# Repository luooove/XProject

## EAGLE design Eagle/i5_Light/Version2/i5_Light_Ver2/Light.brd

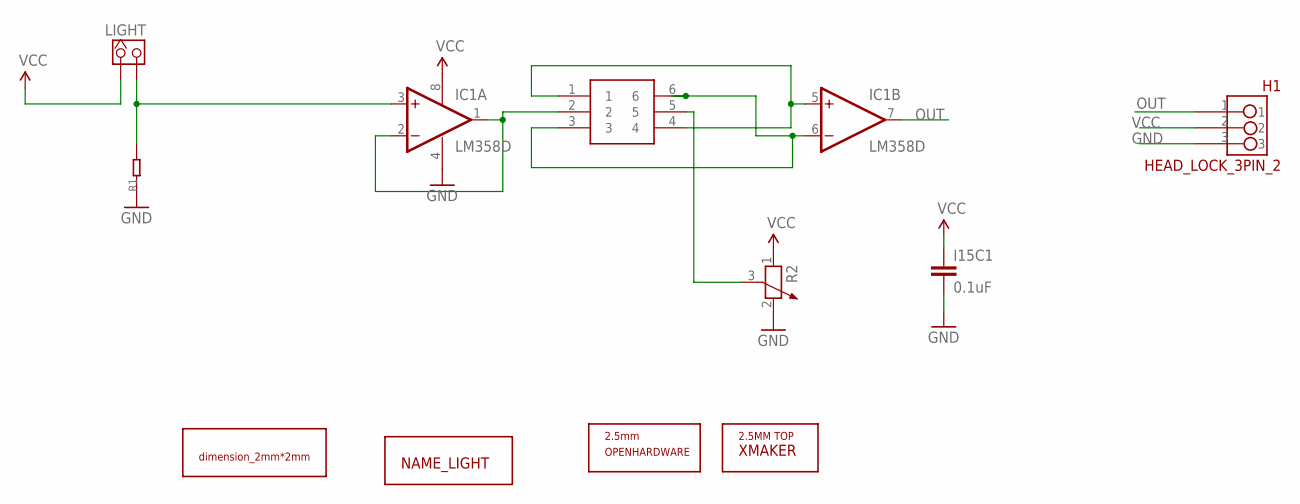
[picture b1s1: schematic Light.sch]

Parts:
H1: HEAD_LOCK_3PIN_2
I15C1: 0.1uF; 0603-CAP
IC1: LM358D; SO08
LIGHT: HEADER_1X2_2.54; CK_1*2
R1: R0603; 0603
R2: R-POTENTIOMETER3362; 3P-SQUA-7X6.8
U$1: DIMENSION_2MM2MM; DIMENSION_2MM*2MM
U$2: NAME_LIGHT
U$3: OPENHARDWARE_2.5MM_TOP; OPENSOURCELOGO_2.5MM
U$4: XMAKERLOGO_2.5MM_TOP
U$5: MSS-22C02

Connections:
GND: H1.3, I15C1.2, IC1.4 (V-), R1.1, R2.2
unnamed: IC1.1 (OUT), IC1.2 (-IN), U$5.2
unnamed: IC1.3 (+IN), LIGHT.2, R1.2
unnamed: IC1.5 (+IN), U$5.1, U$5.4
unnamed: R2.3, U$5.5
unnamed: IC1.6 (-IN), U$5.3, U$5.6
OUT: H1.1, IC1.7 (OUT)
VCC: H1.2, I15C1.1, IC1.8 (V+), LIGHT.1, R2.1

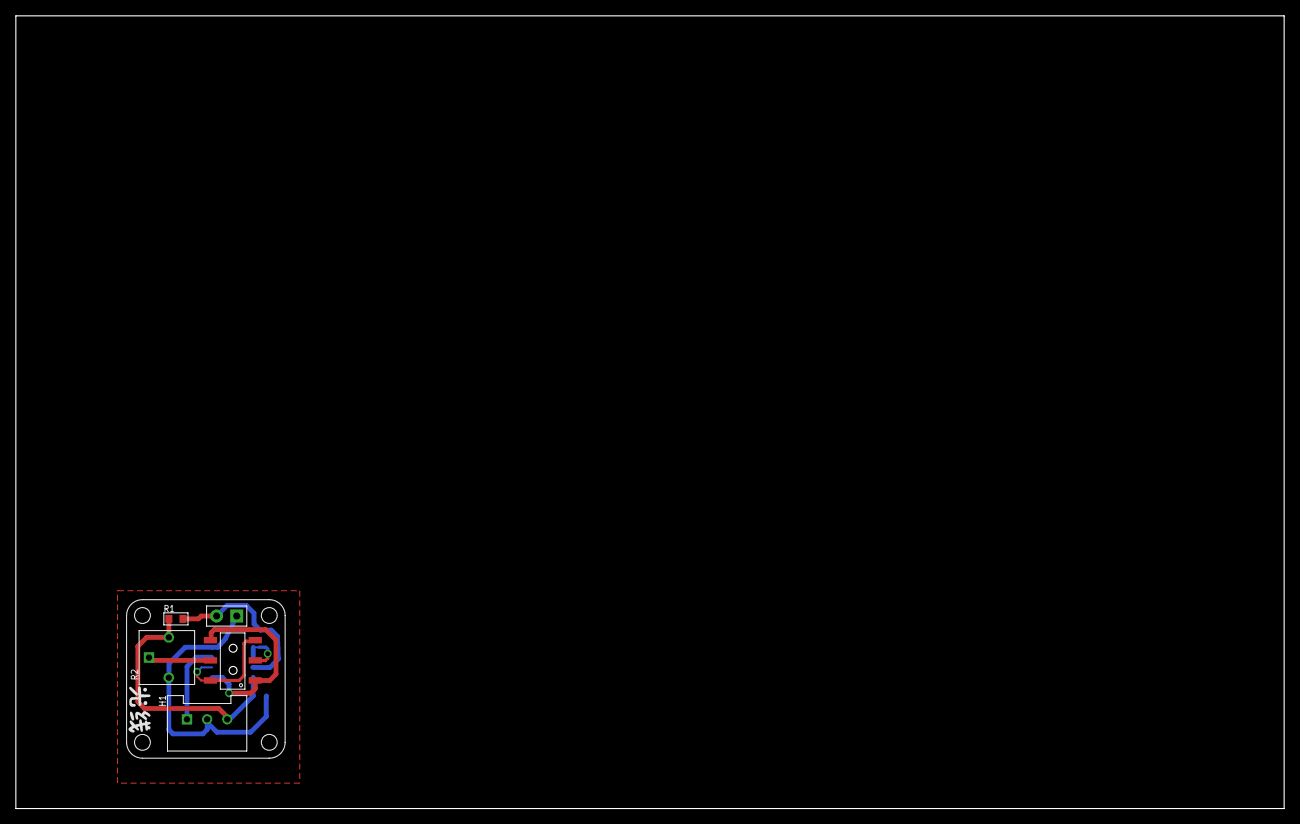
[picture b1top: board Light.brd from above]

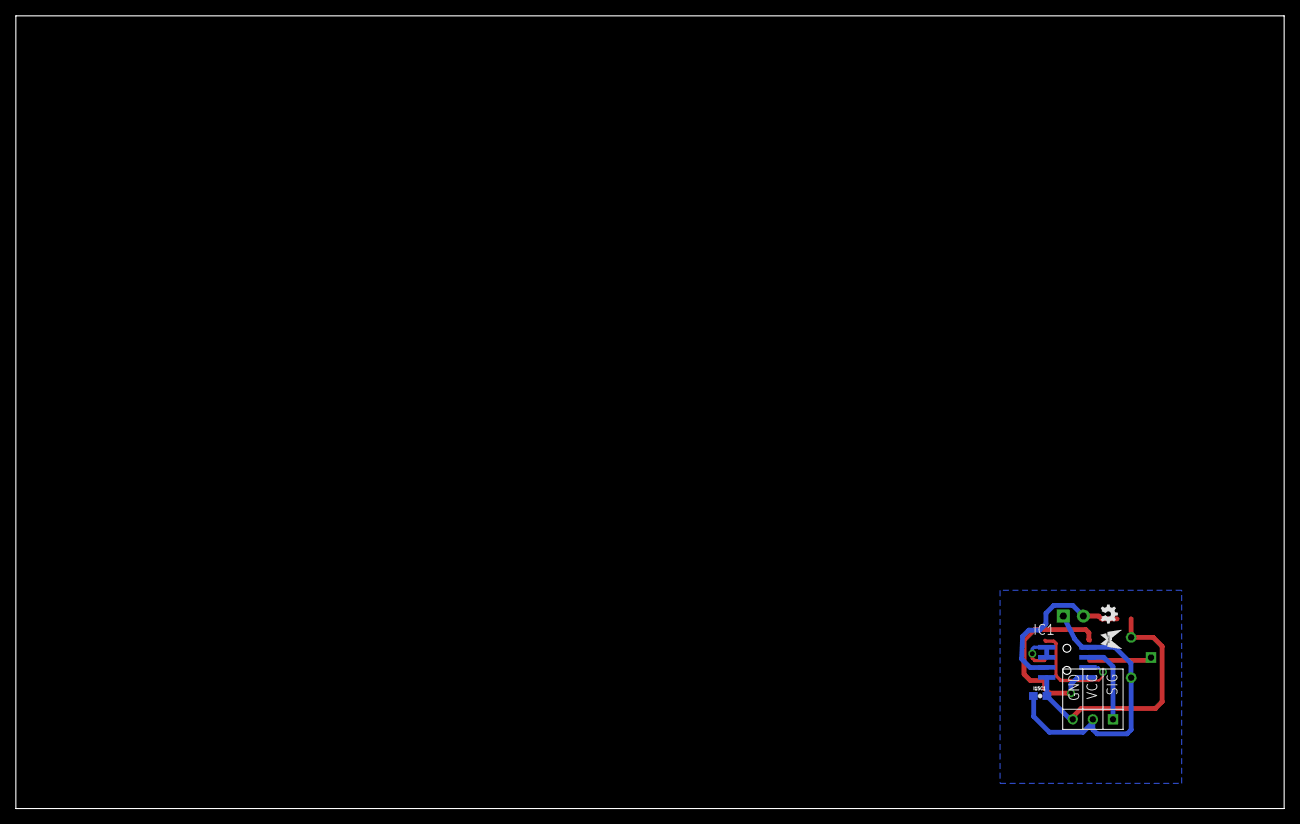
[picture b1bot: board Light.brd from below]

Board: 2 copper layers, 160.0 x 100.0 mm, 11 parts (4 on the bottom side), 8 nets.

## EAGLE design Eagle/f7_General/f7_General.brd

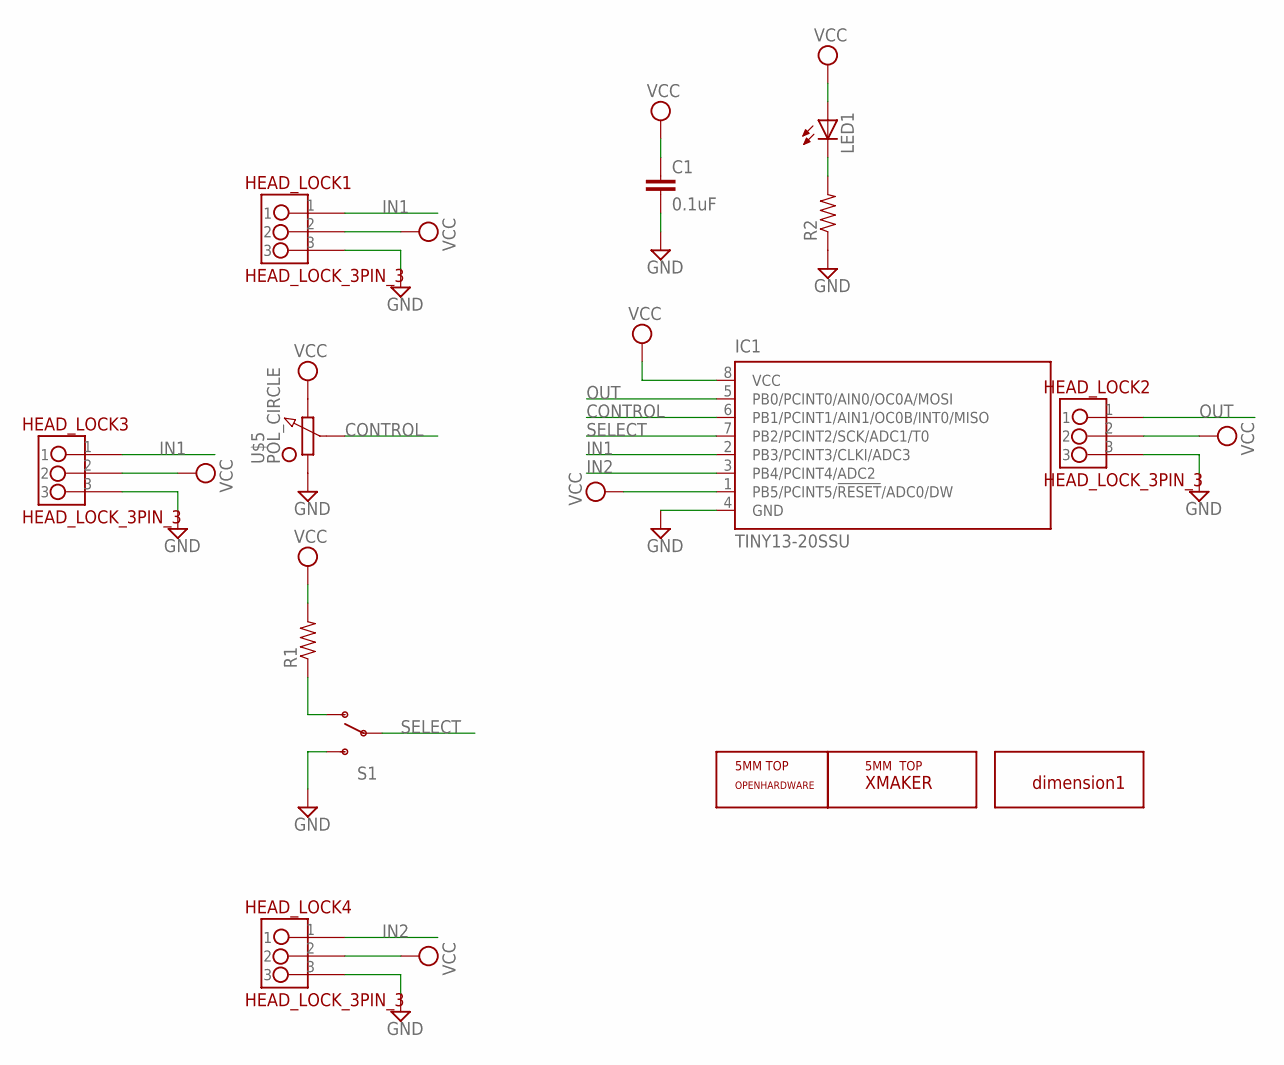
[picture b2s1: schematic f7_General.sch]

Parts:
C1: 0.1uF; 0603-CAP
HEAD_LOCK1, HEAD_LOCK2, HEAD_LOCK3, HEAD_LOCK4: HEAD_LOCK_3PIN_3
IC1: TINY13-20SSU; 8S1
LED1: LED_ESML0603; LED_SML0603
R1: RESISTOR0603-RES; 0603-RES
R2: 0.27OHM-1/10W-1%(0603); 0603-RES
S1: SWITCH-SPDTKIT; SWITCH-SPDT_KIT
U$2: XMAKERLOGO_5MM_TOP
U$3: DIMENSION1
U$4: OPENHARDWARE_5MM_TOP; OPENSOURCE_5MM_TOP
U$5: POL_CIRCLE; POT_CIRCLE

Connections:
CONTROL: IC1.6 (PB1/PCINT1/AIN1/OC0B/INT0/MISO), U$5.P$2 (2)
GND: C1.2, HEAD_LOCK1.3, HEAD_LOCK2.3, HEAD_LOCK3.3, HEAD_LOCK4.3, IC1.4 (GND), R2.1, S1.3 (S), U$5.P$3 (3)
IN1: HEAD_LOCK1.1, HEAD_LOCK3.1, IC1.2 (PB3/PCINT3/CLKI/ADC3)
IN2: HEAD_LOCK4.1, IC1.3 (PB4/PCINT4/ADC2)
unnamed: LED1.C, R2.2
unnamed: R1.1, S1.1 (O)
OUT: HEAD_LOCK2.1, IC1.5 (PB0/PCINT0/AIN0/OC0A/MOSI)
SELECT: IC1.7 (PB2/PCINT2/SCK/ADC1/T0), S1.2
VCC: C1.1, HEAD_LOCK1.2, HEAD_LOCK2.2, HEAD_LOCK3.2, HEAD_LOCK4.2, IC1.1 (PB5/PCINT5/!RESET!/ADC0/DW), IC1.8 (VCC), LED1.A, R1.2, U$5.P$1 (1)

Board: 2 copper layers, 14 parts (0 on the bottom side), 9 nets, no tracks yet.

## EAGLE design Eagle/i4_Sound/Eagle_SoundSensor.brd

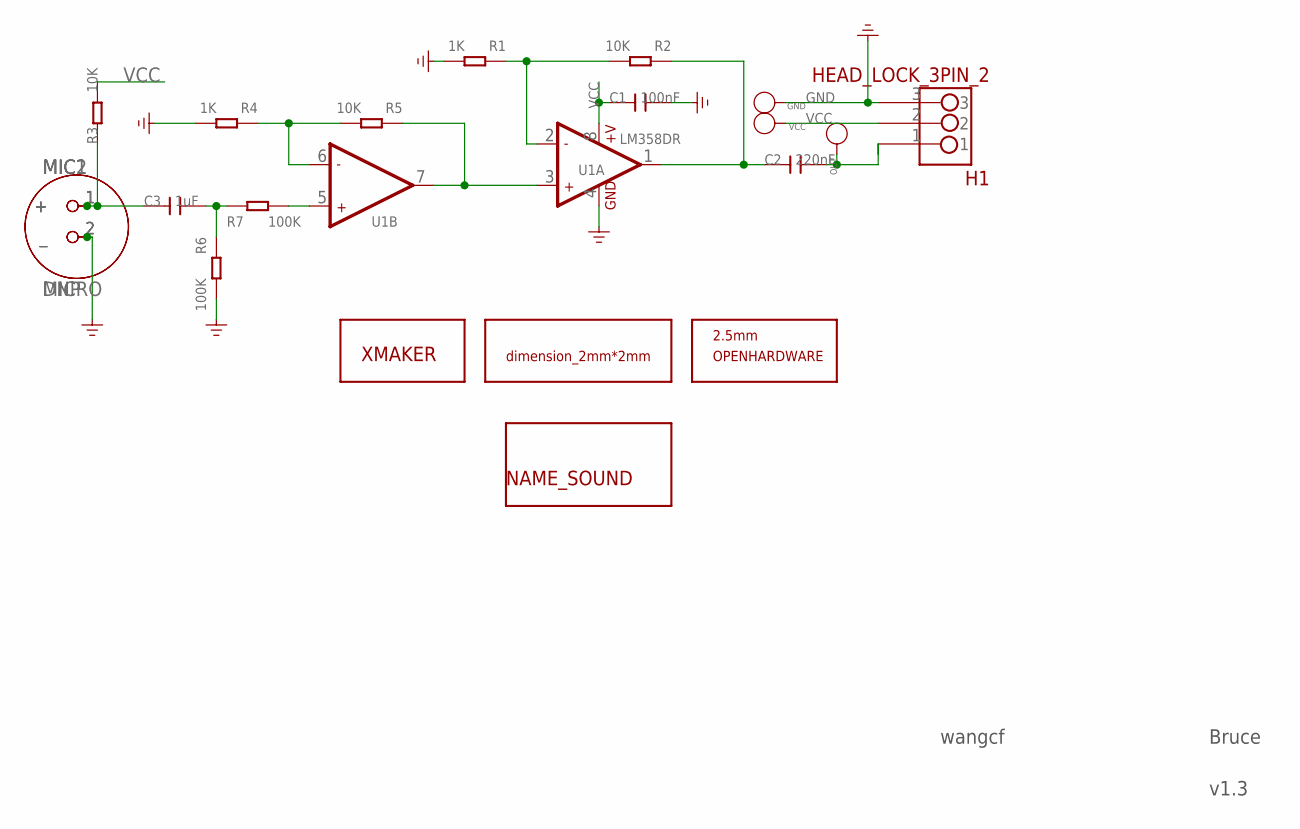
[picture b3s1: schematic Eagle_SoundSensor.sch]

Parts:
C1: 100nF; C0603
C2: 220nF; C0603
C3: 1uF; C0603
GND: PAD-TEST-POINT'4545'; TP_4545
H1: HEAD_LOCK_3PIN_2
MIC1: MICRO
MIC2: DNP; MICRO
OUT: PAD-TEST-POINT'4545'; TP_4545
R1, R4: 1K; R0603
R2, R3, R5: 10K; R0603
R6, R7: 100K; R0603
U1: LM358DR; SO08
U$7: XMAKERLOGO
U$11: DIMENSION_2MM2MM; DIMENSION_2MM*2MM
U$12: OPENHARDWARE_2.5MM_TOP; OPENSOURCELOGO_2.5MM
U$13: NAME_SOUND
VCC: PAD-TEST-POINT'4545'; TP_4545

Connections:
GND: C1.2, GND.T, H1.3, MIC1.2 (_), MIC2.2 (_), R1.2, R4.2, R6.2, U1.4 (GND)
unnamed: R7.2, U1.5 (+IN2)
unnamed: R4.1, R5.2, U1.6 (-IN2)
unnamed: C3.2, R6.1, R7.1
unnamed: C3.1, MIC1.1 (+), MIC2.1 (+), R3.1
unnamed: R5.1, U1.3 (+IN1), U1.7 (OUT2)
unnamed: R1.1, R2.2, U1.2 (-IN1)
OUT: C2.2, H1.1, OUT.T
OUT1: C2.1, R2.1, U1.1 (OUT1)
VCC: C1.1, H1.2, R3.2, U1.8 (+V), VCC.T

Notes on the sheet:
wangcf
Bruce
v1.3

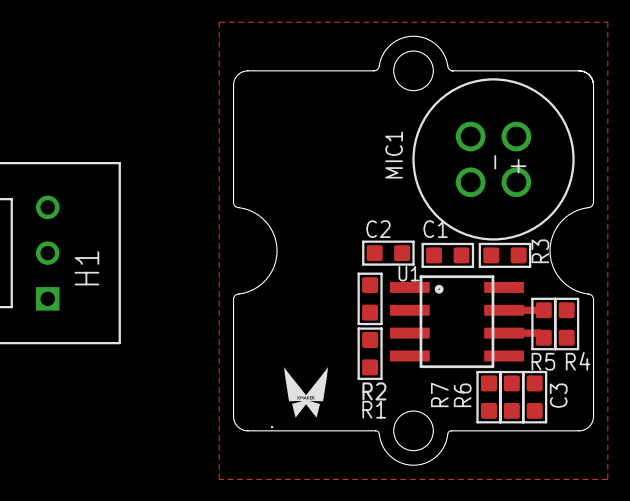
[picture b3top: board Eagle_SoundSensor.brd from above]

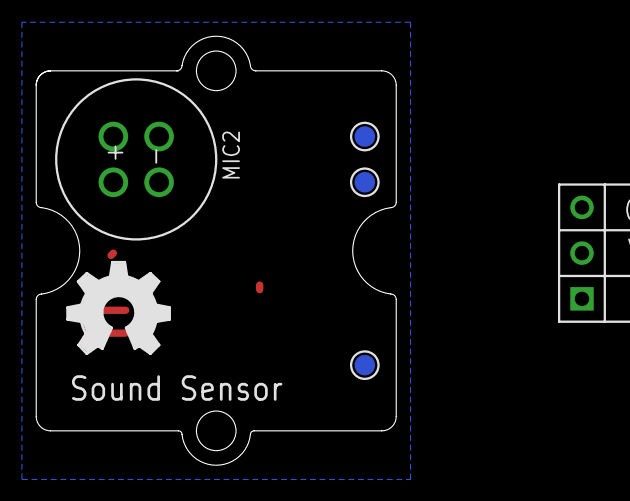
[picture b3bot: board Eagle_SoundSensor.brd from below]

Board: 2 copper layers, 20.0 x 23.8 mm, 23 parts (5 on the bottom side), 10 nets.

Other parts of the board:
U$1: OSHW_FILLX200_NOTEXT
U$4: 1U-DIM-W/-DRILL

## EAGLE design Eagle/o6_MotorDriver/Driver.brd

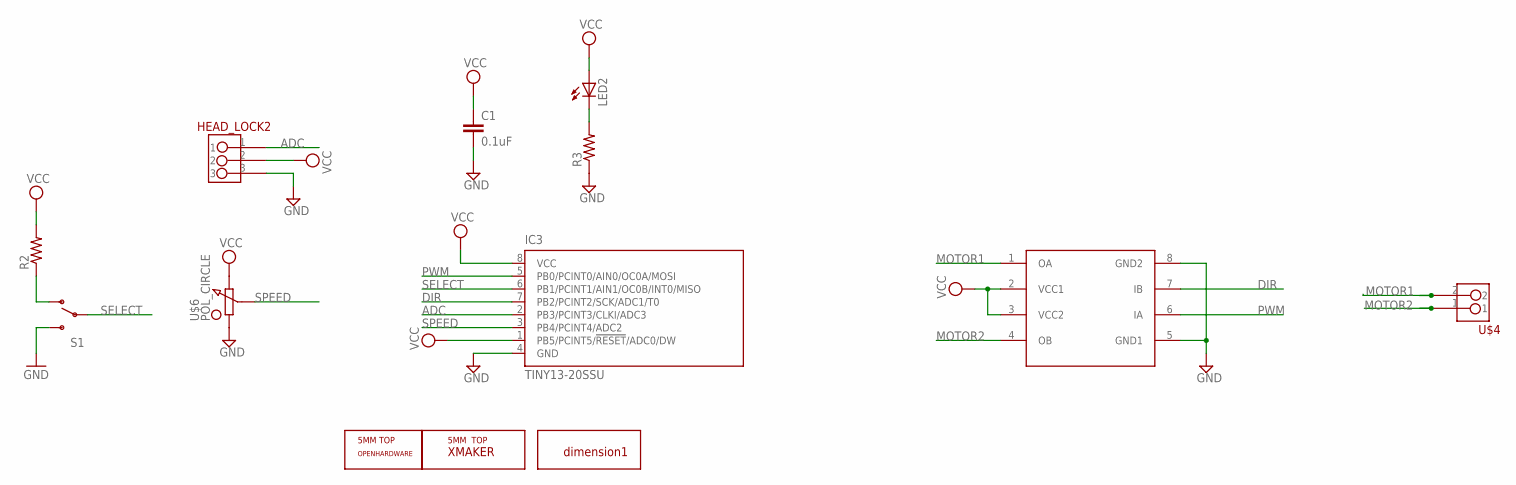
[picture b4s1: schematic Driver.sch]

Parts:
C1: 0.1uF; 0603-CAP
HEAD_LOCK2: HEAD_LOCK
IC3: TINY13-20SSU; 8S1
LED2: LED_ESML0603; LED_SML0603
R2: RESISTOR0603-RES; 0603-RES
R3: 0.27OHM-1/10W-1%(0603); 0603-RES
S1: SWITCH-SPDTKIT; SWITCH-SPDT_KIT
U$1: DIMENSION1
U$2: L9110; SOP8
U$4: HEAD_LOCK2
U$6: POL_CIRCLE; POT_CIRCLE
U$7: XMAKERLOGO_5MM_TOP
U$8: OPENHARDWARE_5MM_TOP; OPENSOURCE_5MM_TOP

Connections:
ADC: HEAD_LOCK2.1, IC3.2 (PB3/PCINT3/CLKI/ADC3)
DIR: IC3.7 (PB2/PCINT2/SCK/ADC1/T0), U$2.7 (IB)
GND: C1.2, HEAD_LOCK2.3, IC3.4 (GND), R3.1, S1.3 (S), U$2.5 (GND1), U$2.8 (GND2), U$6.P$3 (3)
MOTOR1: U$2.1 (OA), U$4.2
MOTOR2: U$2.4 (OB), U$4.1
unnamed: R2.1, S1.1 (O)
unnamed: LED2.C, R3.2
PWM: IC3.5 (PB0/PCINT0/AIN0/OC0A/MOSI), U$2.6 (IA)
SELECT: IC3.6 (PB1/PCINT1/AIN1/OC0B/INT0/MISO), S1.2
SPEED: IC3.3 (PB4/PCINT4/ADC2), U$6.P$2 (2)
VCC: C1.1, HEAD_LOCK2.2, IC3.1 (PB5/PCINT5/!RESET!/ADC0/DW), IC3.8 (VCC), LED2.A, R2.2, U$2.2 (VCC1), U$2.3 (VCC2), U$6.P$1 (1)

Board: 2 copper layers, 13 parts (0 on the bottom side), 11 nets, no tracks yet.

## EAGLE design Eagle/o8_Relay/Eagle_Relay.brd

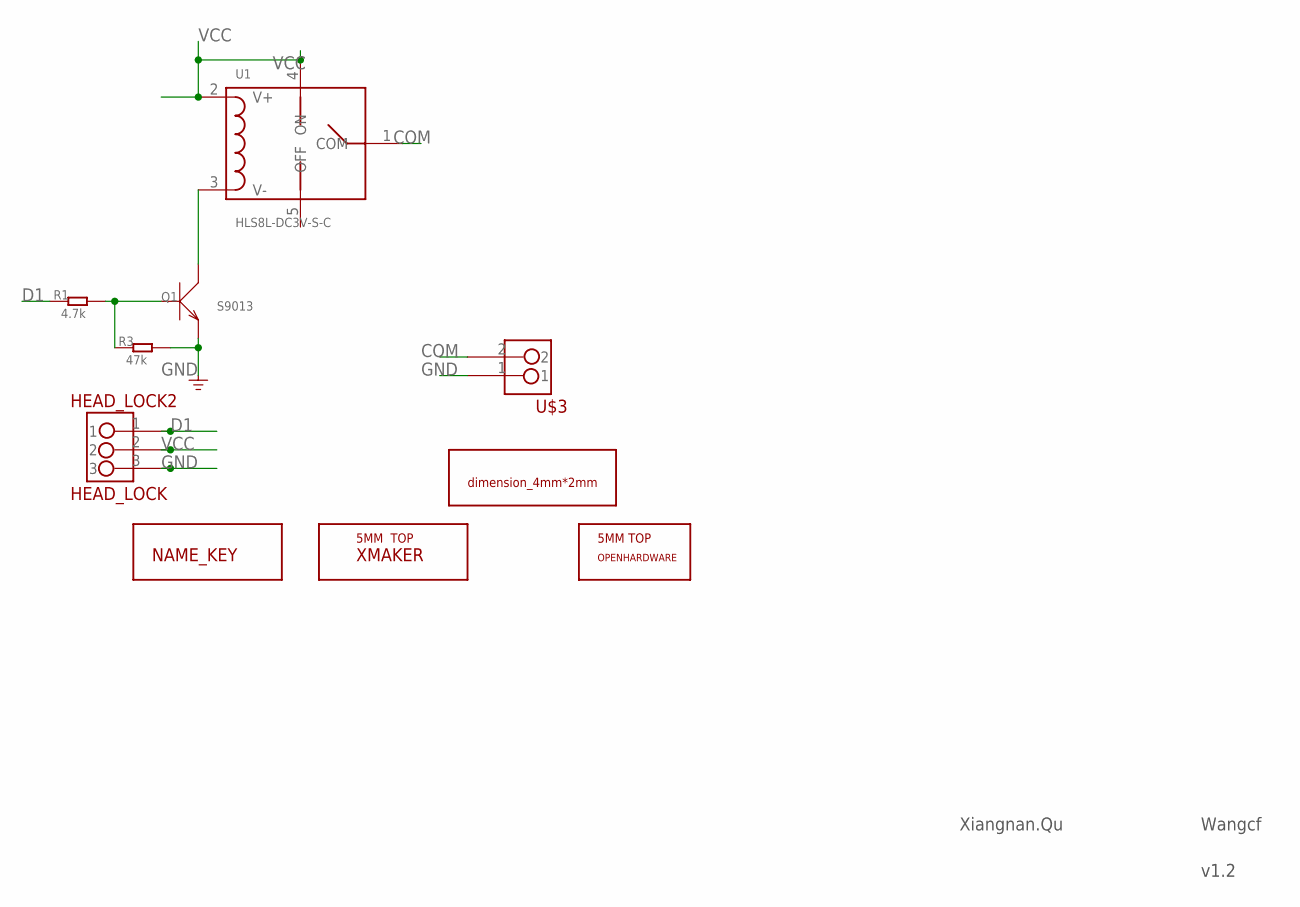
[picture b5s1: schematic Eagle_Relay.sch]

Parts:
HEAD_LOCK2: HEAD_LOCK
Q1: S9013; SOT23
R1: 4.7k; R0603
R3: 47k; R0603
U1: HLS8L-DC3V-S-C; RELAY
U$2: XMAKERLOGO_5MM_TOP
U$3: HEAD_LOCK2
U$5: NAME_RELAY
U$6: DIMENSION_4MM2MM; DIMENSION_2MM*4MM
U$8: OPENHARDWARE_5MM_TOP; OPENSOURCE_5MM_TOP

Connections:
COM: U1.1 (COM), U$3.2
D1: HEAD_LOCK2.1, R1.1
GND: HEAD_LOCK2.3, Q1.2 (E), R3.2, U$3.1
unnamed: Q1.1 (B), R1.2, R3.1
VCC: HEAD_LOCK2.2, U1.2 (V+), U1.4 (ON)
VGND: Q1.3 (C), U1.3 (V-)

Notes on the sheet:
Xiangnan.Qu
Wangcf
v1.2

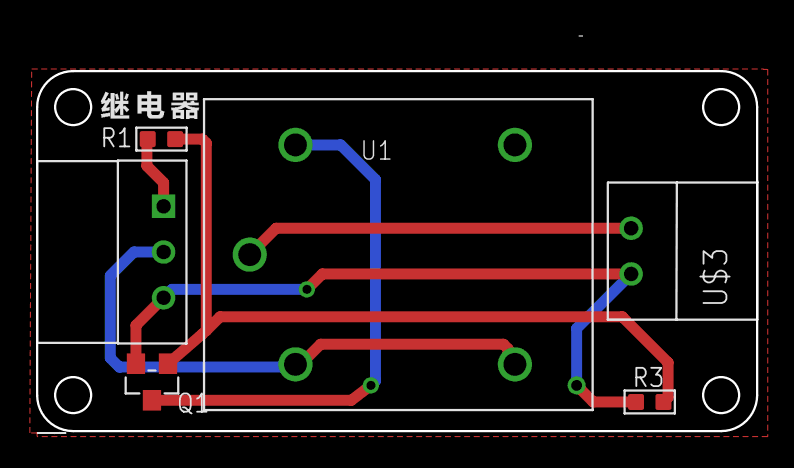
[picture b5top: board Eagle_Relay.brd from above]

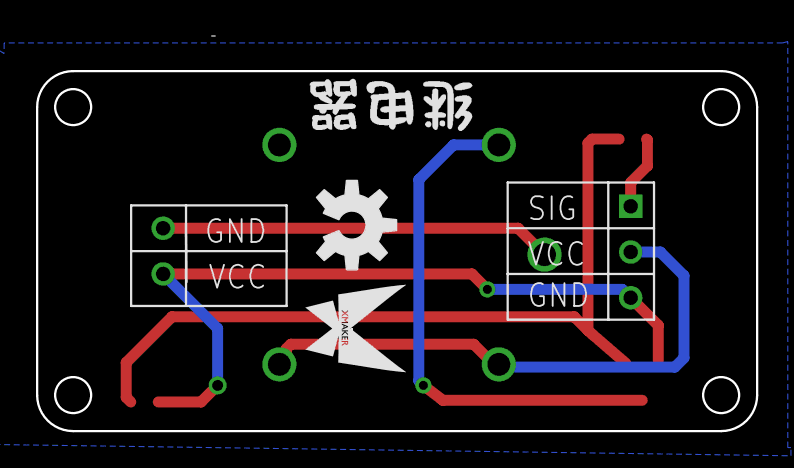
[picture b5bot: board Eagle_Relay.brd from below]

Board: 2 copper layers, 40.0 x 21.9 mm, 10 parts (3 on the bottom side), 6 nets.

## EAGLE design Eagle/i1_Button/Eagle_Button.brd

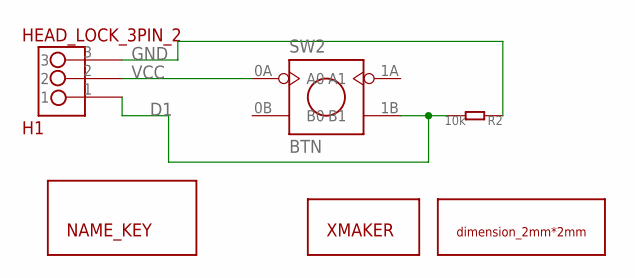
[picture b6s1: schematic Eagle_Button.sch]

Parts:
H1: HEAD_LOCK_3PIN_2
R2: 10k; 0603
SW2: BTN; BTN_8X8
U$1: XMAKERLOGO
U$3: NAME_KEY
U$4: DIMENSION_2MM2MM; DIMENSION_2MM*2MM

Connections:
D1: H1.1, R2.2, SW2.1B (B1)
GND: H1.3, R2.1
VCC: H1.2, SW2.0A (A0)

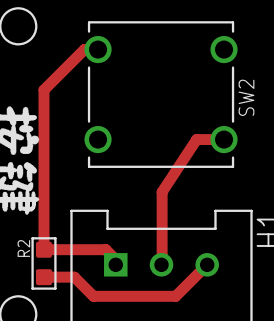
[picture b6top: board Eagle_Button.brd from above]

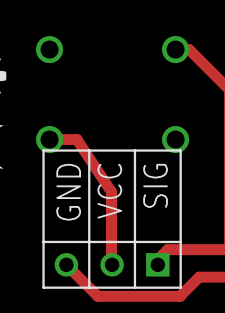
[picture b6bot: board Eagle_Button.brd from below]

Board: 2 copper layers, 7 parts (2 on the bottom side), 3 nets.

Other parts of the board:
U$2: OSHW-LOGO-S

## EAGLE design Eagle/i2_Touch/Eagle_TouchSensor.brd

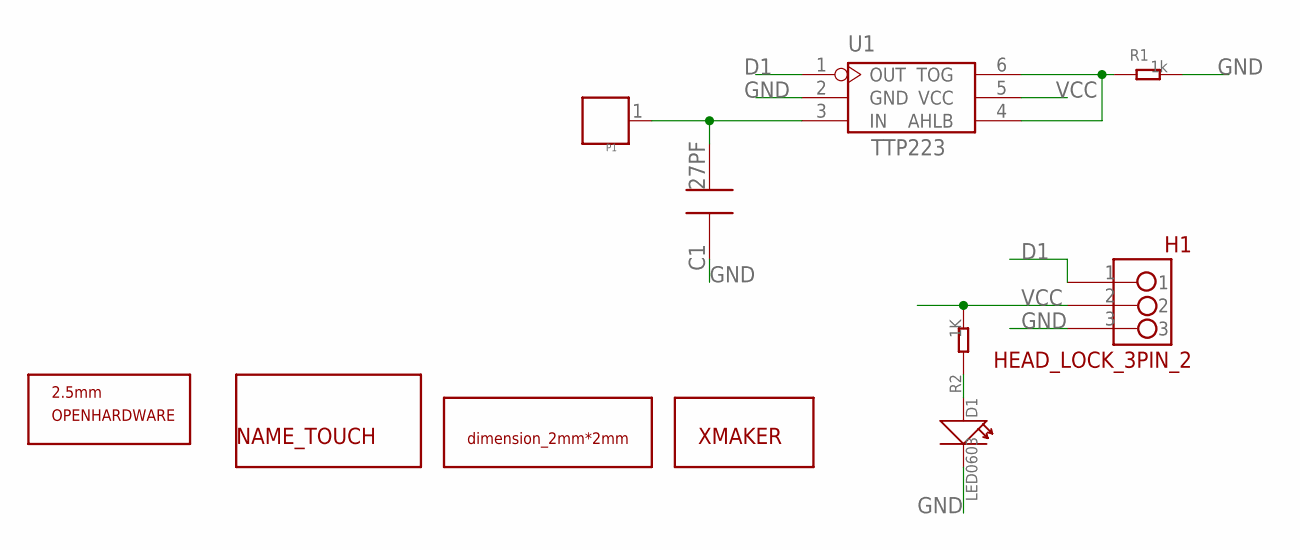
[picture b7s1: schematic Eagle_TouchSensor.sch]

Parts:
C1: 27PF; 0603
D1: LED0603
H1: HEAD_LOCK_3PIN_2
P1: PAD'D450MIL'; 1P-D450
R1: 1k; 0603
R2: 1K; 0603
U1: TTP223; SOT23-6L
U$1: XMAKERLOGO
U$3: DIMENSION_2MM2MM; DIMENSION_2MM*2MM
U$4: NAME_TOUCH
U$5: OPENHARDWARE_2.5MM_TOP; OPENSOURCELOGO_2.5MM

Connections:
D1: H1.1, U1.1 (OUT)
GND: C1.1, D1.2 (-), H1.3, R1.2, U1.2 (GND)
IN: C1.2, P1.1, U1.3 (IN)
unnamed: R1.1, U1.4 (AHLB), U1.6 (TOG)
unnamed: D1.1 (+), R2.1
VCC: H1.2, R2.2, U1.5 (VCC)

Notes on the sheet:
TTP223

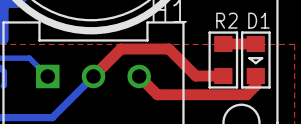
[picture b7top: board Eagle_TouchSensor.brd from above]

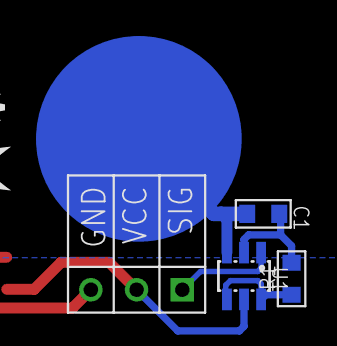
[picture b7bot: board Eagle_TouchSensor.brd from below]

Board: 2 copper layers, 11 parts (6 on the bottom side), 6 nets.

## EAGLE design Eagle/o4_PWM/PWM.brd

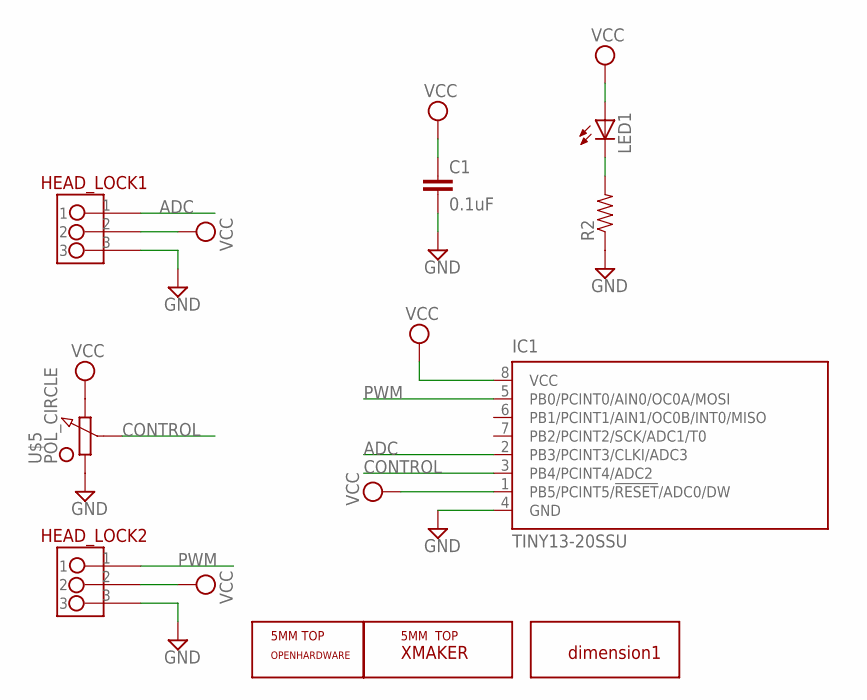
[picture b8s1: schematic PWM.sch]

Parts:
C1: 0.1uF; 0603-CAP
HEAD_LOCK1, HEAD_LOCK2: HEAD_LOCK
IC1: TINY13-20SSU; 8S1
LED1: LED_ESML0603; LED_SML0603
R2: 0.27OHM-1/10W-1%(0603); 0603-RES
U$2: XMAKERLOGO_5MM_TOP
U$3: DIMENSION1
U$4: OPENHARDWARE_5MM_TOP; OPENSOURCE_5MM_TOP
U$5: POL_CIRCLE; POT_CIRCLE

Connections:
ADC: HEAD_LOCK1.1, IC1.2 (PB3/PCINT3/CLKI/ADC3)
CONTROL: IC1.3 (PB4/PCINT4/ADC2), U$5.P$2 (2)
GND: C1.2, HEAD_LOCK1.3, HEAD_LOCK2.3, IC1.4 (GND), R2.1, U$5.P$3 (3)
unnamed: LED1.C, R2.2
PWM: HEAD_LOCK2.1, IC1.5 (PB0/PCINT0/AIN0/OC0A/MOSI)
VCC: C1.1, HEAD_LOCK1.2, HEAD_LOCK2.2, IC1.1 (PB5/PCINT5/!RESET!/ADC0/DW), IC1.8 (VCC), LED1.A, U$5.P$1 (1)

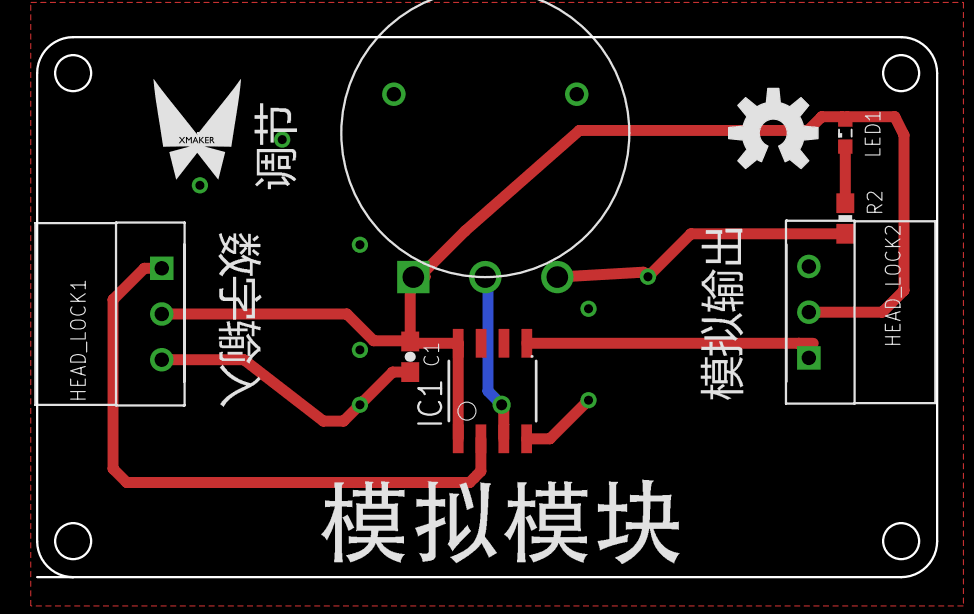
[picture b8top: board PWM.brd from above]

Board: 2 copper layers, 50.0 x 30.0 mm, 10 parts (0 on the bottom side), 6 nets.

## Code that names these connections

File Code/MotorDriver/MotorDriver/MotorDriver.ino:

//                      +-\/-+
// [RST]ADC0 (D 5) PB5 1|    |8 Vcc
//      ADC3 (D 3) PB3 2|    |7 PB2 (D 2) ADC1[SCK]
//      ADC2 (D 4) PB4 3|    |6 PB1 (D 1) PWM1[MISO]
//                 GND 4|    |5 PB0 (D 0) PWM0[MOSI]
//                      +----+

void setup() {
  // put your setup code here, to run once:
  pinMode(2, OUTPUT);  //dir

}

void loop() {
 // put your main code here, to run repeatedly:
  if (digitalRead(3) == 0)
  {
    if (digitalRead(1) == 1)
    {
      digitalWrite(2, HIGH);
      analogWrite(0, 255 - analogRead(2) / 4); //some problem in this pin
    }

    else
    {
      digitalWrite(2, LOW);
      analogWrite(0, analogRead(2) / 4); //some problem in this pin
    }

  }
  else
  {
    digitalWrite(2, LOW);
    analogWrite(0, 0);
  }
}

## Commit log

2015-11-11 :tada: Added .gitattributes & .gitignore files
2015-11-11 main
2015-11-11 add if
2015-11-11 add compare
2015-11-11 add delay
2015-11-11 add pwm
2015-12-05 ad
    a
2015-12-05 添加 编号
2015-12-05 添加编号 txt
2015-12-08 move
2015-12-08 Update 编号.txt
    wire to function
2015-12-08 add motor driver
2015-12-09 第一次更新
2015-12-09 数码管显示
2015-12-14 change motordriver
2015-12-14 miniuno
2015-12-14 gxzz
2015-12-14 light sensor update
2015-12-14 12.15
2015-12-15 head to h
2015-12-15 添加 文字丝印库
2015-12-15 调整按键
2015-12-15 chuange touch
2015-12-15 调整蜂鸣器
2015-12-16 light
2015-12-17 添加电源模块
2015-12-17 添加非模块等
2015-12-17 添加电机
2015-12-17 更新模拟模块
2015-12-17 添加文字2
2015-12-17 模拟修改
2015-12-18 general
2015-12-21 update lib
2016-01-07 2016年1月7日
2016-01-16 调整电机驱动模块
2016-01-21 slideswitch

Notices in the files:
parts and their libraries:
SparkFun-Passives: Licensing: Creative Commons ShareAlike 4.0 International - https://creativecommons.org/licenses/by-sa/4.0
